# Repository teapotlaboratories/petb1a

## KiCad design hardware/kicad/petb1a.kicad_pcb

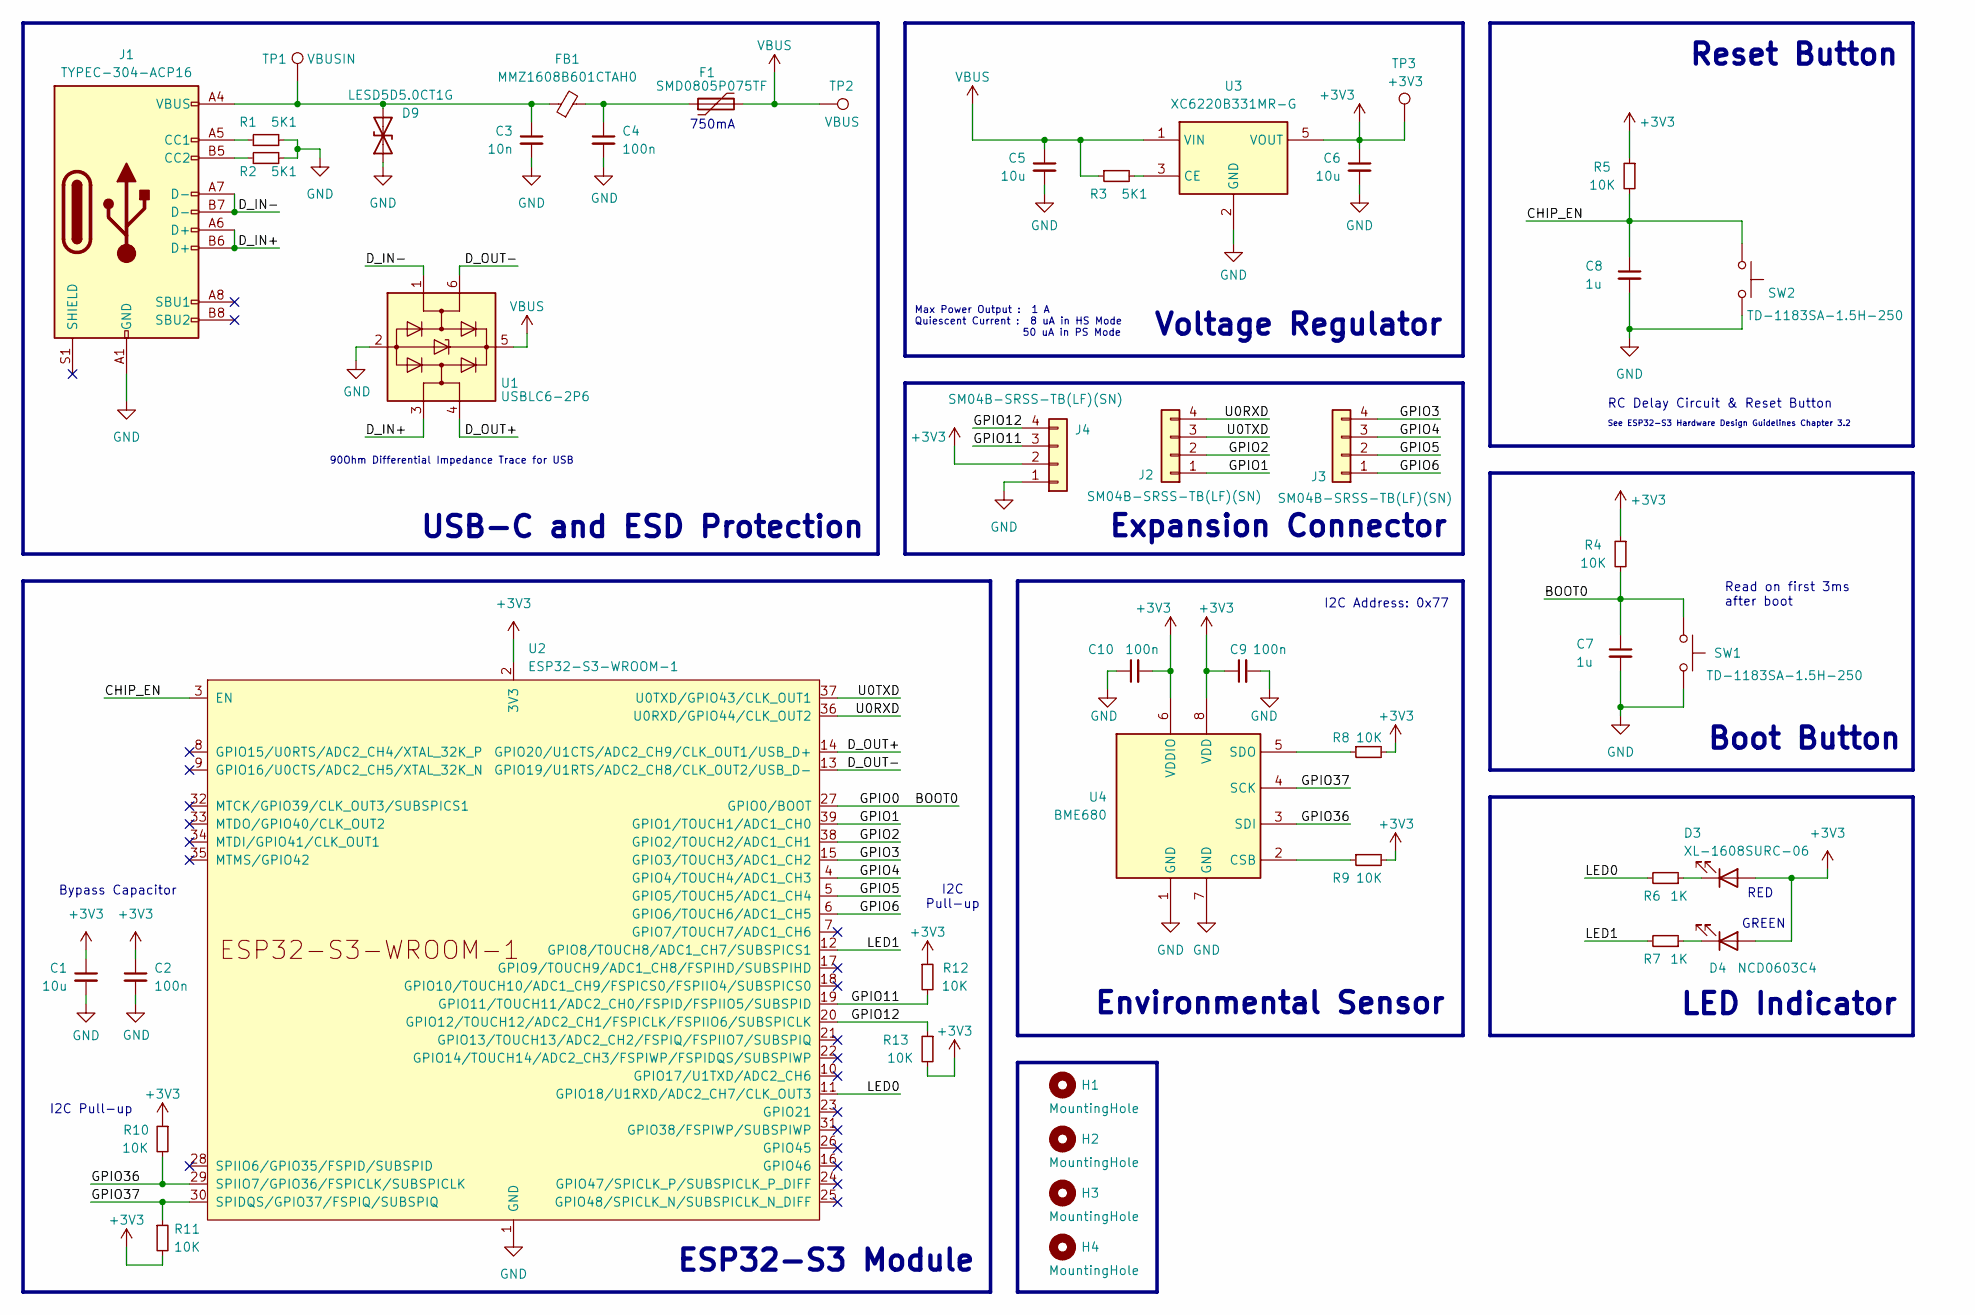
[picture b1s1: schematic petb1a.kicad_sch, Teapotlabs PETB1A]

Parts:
C1, C5, C6: 10u; C_0603_1608Metric; Manufacturer Part Number CL10A106KP8NNNC
C2, C4: 100n; C_0603_1608Metric; Manufacturer Part Number CL10B104KB8NNNC
C3: 10n; C_0603_1608Metric; Manufacturer Part Number CC0603KRX7R9BB103
C7, C8: 1u; C_0402_1005Metric; Manufacturer Part Number GRM155Z71A105KE01D
C9, C10: 100n; C_0402_1005Metric; Manufacturer Part Number GRM155R71H104KE14D
D3: XL-1608SURC-06; LED_0603_1608Metric; Manufacturer Part Number XL-1608SURC-06
D4: NCD0603C4; LED_0603_1608Metric; Manufacturer Part Number NCD0603C4
D9: LESD5D5.0CT1G; D_SOD-523; Manufacturer Part Number LESD5D5.0CT1G
F1: SMD0805P075TF; Fuse_0805_2012Metric; Manufacturer Part Number SMD0805P075TF
FB1: MMZ1608B601CTAH0; L_0603_1608Metric; Manufacturer Part Number MMZ1608B601CTAH0
H1, H2, H3, H4: MountingHole; MountingHole_3.2mm_M3
J1: TYPEC-304-ACP16; USB-C-SMD_TYPE-C-16P-1; Manufacturer Part Number TYPEC-304-ACP16
J2, J3, J4: SM04B-SRSS-TB(LF)(SN); JST_SH_SM04B-SRSS-TB_1x04-1MP_P1.00mm_Horizontal; Manufacturer Part Number SM04B-SRSS-TB(LF)(SN)
R1, R2, R3: 5K1; R_0402_1005Metric; Manufacturer Part Number 0402WGF5101TCE
R4, R5, R8, R9, R10, R11, R12, R13: 10K; R_0402_1005Metric; Manufacturer Part Number 0402WGF1002TCE
R6, R7: 1K; R_0603_1608Metric; Manufacturer Part Number RC0603FR-071KL
SW1, SW2: TD-1183SA-1.5H-250; KEY-SMD_L3.0-W2.5-LS4.0; Manufacturer Part Number TD-1183SA-1.5H-250
TP1: VBUSIN; TestPoint_Pad_D1.0mm
TP2: VBUS; TestPoint_Pad_D1.0mm
TP3: +3V3; TestPoint_Pad_D1.0mm
U1: USBLC6-2P6; SOT-666; Manufacturer Part Number USBLC6-2P6
U2: ESP32-S3-WROOM-1; Manufacturer Part Number ESP32-S3-WROOM-1-N16R8
U3: XC6220B331MR-G; SOT-23-5; Manufacturer Part Number XC6220B331MR-G
U4: BME680; Bosch_LGA-8_3x3mm_P0.8mm_ClockwisePinNumbering; Manufacturer Part Number BME688

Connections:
+3V3: C1.1, C2.1, C6.1, C9.1, C10.2, D3.2 (A), D4.2 (A), J4.2, R4.1, R5.1, R8.2, R9.2, R10.1, R11.2, R12.1, R13.2, TP3.1, U2.2 (3V3), U3.5 (VOUT), U4.6 (VDDIO), U4.8 (VDD)
/BOOT0: C7.1, R4.2, SW1.2, U2.27 (GPIO0/BOOT)
/CHIP_EN: C8.1, R5.2, SW2.2, U2.3 (EN)
/D_IN+: J1.A6 (D+), J1.B6 (D+), U1.3 (I/O2)
/D_IN-: J1.A7 (D-), J1.B7 (D-), U1.1 (I/O1)
/D_OUT+: U1.4 (I/O2), U2.14 (GPIO20/U1CTS/ADC2_CH9/CLK_OUT1/USB_D+)
/D_OUT-: U1.6 (I/O1), U2.13 (GPIO19/U1RTS/ADC2_CH8/CLK_OUT2/USB_D-)
/GPIO1: J2.1, U2.39 (GPIO1/TOUCH1/ADC1_CH0)
/GPIO2: J2.2, U2.38 (GPIO2/TOUCH2/ADC1_CH1)
/GPIO3: J3.4, U2.15 (GPIO3/TOUCH3/ADC1_CH2)
/GPIO4: J3.3, U2.4 (GPIO4/TOUCH4/ADC1_CH3)
/GPIO5: J3.2, U2.5 (GPIO5/TOUCH5/ADC1_CH4)
/GPIO6: J3.1, U2.6 (GPIO6/TOUCH6/ADC1_CH5)
/GPIO11: J4.3, R12.2, U2.19 (GPIO11/TOUCH11/ADC2_CH0/FSPID/FSPIIO5/S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)
/GPIO12: J4.4, R13.1, U2.20 (GPIO12/TOUCH12/ADC2_CH1/FSPICLK/FSPIIO6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)
/GPIO36: R10.2, U2.29 (SPIIO7/GPIO36/FSPICLK/SUBSPICLK), U4.3 (SDI)
/GPIO37: R11.1, U2.30 (SPIDQS/GPIO37/FSPIQ/SUBSPIQ), U4.4 (SCK)
/LED0: R6.2, U2.11 (GPIO18/U1RXD/ADC2_CH7/CLK_OUT3)
/LED1: R7.2, U2.12 (GPIO8/TOUCH8/ADC1_CH7/SUBSPICS1)
/U0RXD: J2.4, U2.36 (U0RXD/GPIO44/CLK_OUT2)
/U0TXD: J2.3, U2.37 (U0TXD/GPIO43/CLK_OUT1)
GND: C1.2, C2.2, C3.2, C4.2, C5.2, C6.2, C7.2, C8.2, C9.2, C10.1, J1.A1 (GND), J1.A12 (GND), J1.B1 (GND), J1.B12 (GND), J4.1, R1.2, R2.2, SW1.1, SW2.1, U1.2 (GND), U2.1 (GND), U2.40 (GND), U2.41 (GND), U3.2 (GND), U4.1 (GND), U4.7 (GND); also elsewhere on the board
unnamed: C4.1, F1.1, FB1.2
unnamed 23: C3.1, FB1.1, J1.A4 (VBUS), J1.A9 (VBUS), J1.B4 (VBUS), J1.B9 (VBUS), TP1.1; also elsewhere on the board
unnamed: D3.1 (K), R6.1
unnamed: D4.1 (K), R7.1
unnamed: J1.A5 (CC1), R1.1
unnamed: J1.B5 (CC2), R2.1
unnamed: R3.2, U3.3 (CE)
unnamed: R9.1, U4.2 (CSB)
unnamed: R8.1, U4.5 (SDO)
VBUS: C5.1, F1.2, R3.1, TP2.1, U1.5 (VBUS), U3.1 (VIN)

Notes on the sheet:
LED Indicator
Expansion Connector
Max Power Output : 1 A Quiescent Current : 8 uA in HS Mode 50 uA in PS Mode
RC Delay Circuit & Reset Button
I2C Pull-up
Environmental Sensor
RED
Boot Button
Reset Button
90Ohm Differential Impedance Trace for USB
Bypass Capacitor
I2C Address: 0x77
USB-C and ESD Protection
Voltage Regulator
I2C Pull-up
ESP32-S3 Module
Read on first 3ms after boot
See ESP32-S3 Hardware Design Guidelines Chapter 3.2
750mA
GREEN

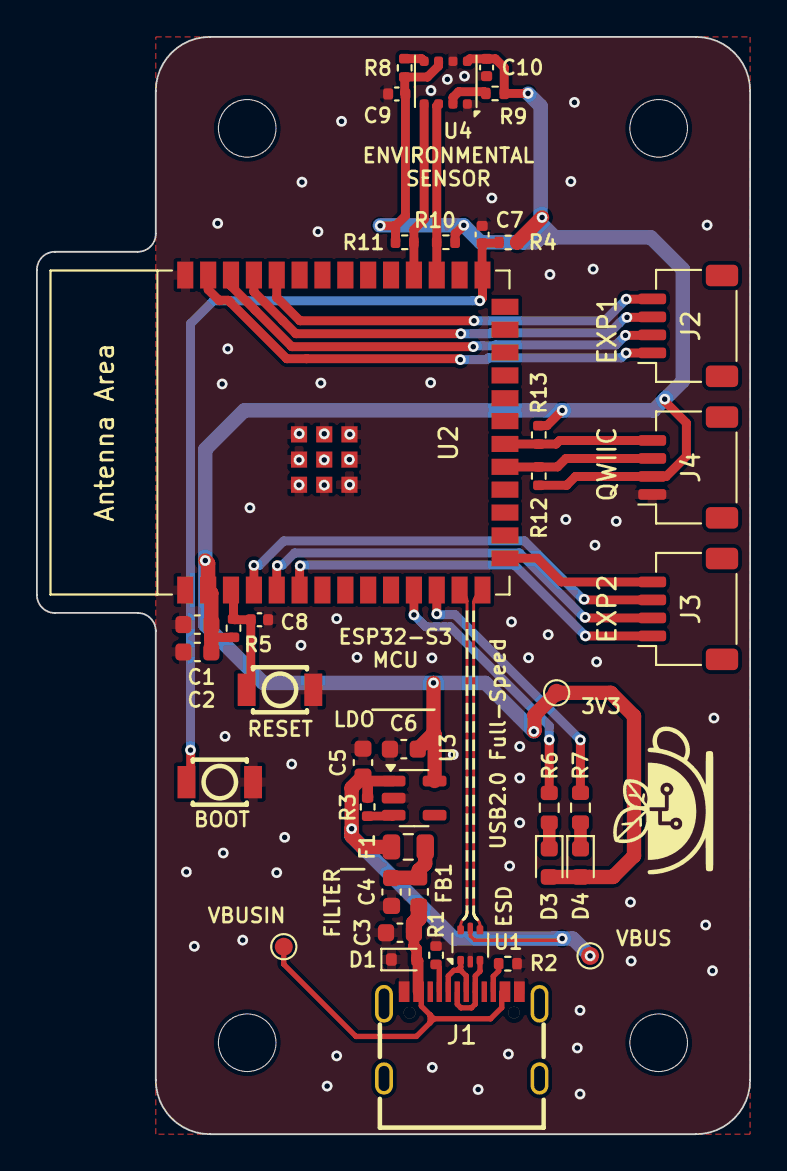
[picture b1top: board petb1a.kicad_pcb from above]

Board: 4 copper layers, 39.6 x 61.0 mm, 45 parts (0 on the bottom side), 32 nets.

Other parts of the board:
D1: LESD5D5.0CT1G; D_SOD-523

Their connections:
GND: D1.1 (A1); also elsewhere on the board
unnamed 23: D1.2 (A2); also elsewhere on the board

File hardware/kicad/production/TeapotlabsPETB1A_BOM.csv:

Id,Designator,Quantity,Manufacturer,Manufacturer Part Number,Value,Description,Footprint,Type,Distributor,Distributor Part Number,Distributor Link,Datasheet
1,"C1,C5,C6",3,Samsung Electro-Mechanics,CL10A106KP8NNNC,10u,Ceramic Capacitor 10V 10uF X5R ±10%,C_0603_1608Metric,SMD,LCSC,C19702,https://www.lcsc.com/product-detail/Multilayer-Ceramic-Capac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,https://datasheet.lcsc.com/lcsc/2304140030_Samsung-Electro-M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
2,"C2,C4",2,Samsung Electro-Mechanics,CL10B104KB8NNNC,100n,Ceramic Capacitor 50V 100nF X7R ±10%,C_0603_1608Metric,SMD,LCSC,C1591,https://www.lcsc.com/product-detail/Multilayer-Ceramic-Capac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,https://datasheet.lcsc.com/lcsc/2304140030_Samsung-Electro-M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
3,C3,1,YAGEO,CC0603KRX7R9BB103,10n,Ceramic Capacitors 50V 10nF X7R ±10%,C_0603_1608Metric,SMD,LCSC,C100042,https://www.lcsc.com/product-detail/Multilayer-Ceramic-Capac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,https://datasheet.lcsc.com/lcsc/2304140030_YAGEO-CC0603KRX7R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
4,"C7,C8",2,Murata Electronics,GRM155Z71A105KE01D,1u,Ceramic Capacitors 10V 1uF X7R ±10%,C_0402_1005Metric,SMD,LCSC,C528974,https://www.lcsc.com/product-detail/Multilayer-Ceramic-Capac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,https://datasheet.lcsc.com/lcsc/2005261833_Murata-Electronic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
5,"C9,C10",2,Murata Electronics,GRM155R71H104KE14D,100n,Ceramic Capacitors 50V 100nF X7R,C_0402_1005Metric,SMD,LCSC,C77020,https://www.lcsc.com/product-detail/Multilayer-Ceramic-Capac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,https://datasheet.lcsc.com/lcsc/1809272047_Murata-Electronic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
6,D1,1,LRC,LESD5D5.0CT1G,LESD5D5.0CT1G,ESD 9.4A 18.6V 5.6V Bi-Directional 5V,D_SOD-523,SMD,LCSC,C383211,https://www.lcsc.com/product-detail/Electrostatic-and-Surge-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,https://datasheet.lcsc.com/lcsc/1912111437_LRC-LESD5D5-0CT1G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
7,D3,1,XINGLIGHT,XL-1608SURC-06,XL-1608SURC-06,LED Red 120° 55mW 25mA ,LED_0603_1608Metric,SMD,LCSC,C965799,https://www.lcsc.com/product-detail/Light-Emitting-Diodes-sp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,https://datasheet.lcsc.com/lcsc/2402181505_XINGLIGHT-XL-1608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
8,D4,1,Foshan NationStar Optoelectronics,NCD0603C4,NCD0603C4,LED Green-yellow 140° 65mW 1.6V~2.6V,LED_0603_1608Metric,SMD,LCSC,C7429911,https://www.lcsc.com/product-detail/Light-Emitting-Diodes-sp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,https://datasheet.lcsc.com/lcsc/2306200951_Foshan-NationStar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
9,F1,1,RUILON(Shenzhen Ruilongyuan Elec),SMD0805P075TF,SMD0805P075TF,Resettable Fuses 6V 750mA 40A 1.5A,Fuse_0805_2012Metric,SMD,LCSC,C20979,https://www.lcsc.com/product-detail/Resettable-Fuses_RUILON-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,https://datasheet.lcsc.com/lcsc/2304140030_RUILON-Shenzhen-R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
10,FB1,1,TDK,MMZ1608B601CTAH0,MMZ1608B601CTAH0,Ferrite Beads 400mΩ ±25% 600Ω@100MHz,L_0603_1608Metric,SMD,LCSC,C97120,https://www.lcsc.com/product-detail/Ferrite-Beads_TDK-MMZ160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,https://datasheet.lcsc.com/lcsc/2304140030_TDK-MMZ1608B601CT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
11,J1,1,XUNPU,TYPEC-304-ACP16,TYPEC-304-ACP16,Type-C SMD 3A 1 Surface Mount，Right Angle 16P Female,USB-C-SMD_TYPE-C-16P-1,SMD,LCSC,C2982555,https://www.lcsc.com/product-detail/USB-Connectors_XUNPU-TYP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,https://datasheet.lcsc.com/lcsc/2203111830_XUNPU-TYPEC-304-A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
12,"J2,J3,J4",3,JST,SM04B-SRSS-TB(LF)(SN), SM04B-SRSS-TB(LF)(SN),Right Angle Wire To Board 1x4P 4P 1mm 1A,JST_SH_SM04B-SRSS-TB_1x04-1MP_P1.00mm_Horizontal,SMD,LCSC,C160404,https://www.lcsc.com/product-detail/Wire-To-Board-Wire-To-Wi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,https://datasheet.lcsc.com/lcsc/2304140030_JST-Sales-America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
13,"R1,R2,R3",3,UNI-ROYAL(Uniroyal Elec),0402WGF5101TCE,5K1,Resistor 62.5mW ±1% 5.1kΩ,R_0402_1005Metric,SMD,LCSC,C25905,https://www.lcsc.com/product-detail/Chip-Resistor-Surface-Mo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,https://datasheet.lcsc.com/lcsc/2206010045_UNI-ROYAL-Uniroya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
14,"R4,R5,R8,R9,R10,R11,R12,R13",8,UNI-ROYAL(Uniroyal Elec),0402WGF1002TCE,10K,Resistors 62.5mW ±1% 10kΩ,R_0402_1005Metric,SMD,LCSC,C25744,https://www.lcsc.com/product-detail/Chip-Resistor-Surface-Mo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,https://datasheet.lcsc.com/lcsc/2206010100_UNI-ROYAL-Uniroya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
15,"R6,R7",2,YAGEO,RC0603FR-071KL,1K,Resistor 100mW 75V ±1% 1kΩ,R_0603_1608Metric,SMD,LCSC,C22548,https://www.lcsc.com/product-detail/Chip-Resistor-Surface-Mo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,https://datasheet.lcsc.com/lcsc/2304140030_YAGEO-RC0603FR-07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
16,"SW1,SW2",2,DEALON,TD-1183SA-1.5H-250,TD-1183SA-1.5H-250,"Tactile Switches 2.5mm 1.5mm 3mm SMD,2.5x3mm ",KEY-SMD_L3.0-W2.5-LS4.0,SMD,LCSC,C2905189,https://www.lcsc.com/product-detail/Tactile-Switches_DEALON-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,https://datasheet.lcsc.com/lcsc/2209081200_DEALON-TD-1183SA-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
17,U1,1,STMicroelectronics,USBLC6-2P6,USBLC6-2P6,ESD Protection 6V 17V 2 Unidirectional 5.25V,SOT-666,SMD,LCSC,C15999,https://www.lcsc.com/product-detail/ESD-Protection-Devices_S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,https://www.st.com/resource/en/datasheet/usblc6-2.pdf
18,U2,1,Espressif Systems,ESP32-S3-WROOM-1-N16R8 ,ESP32-S3-WROOM-1,WiFi Modules ESP32-S3 ,ESP32-S3-WROOM-1,SMD,LCSC,C2913202,https://www.lcsc.com/product-detail/WiFi-Modules_Espressif-S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,https://www.espressif.com/sites/default/files/documentation/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
19,U3,1,Torex Semicon,XC6220B331MR-G,XC6220B331MR-G,LDO 50dB@(1kHz) 1A Fixed 3.3V Positive,SOT-23-5,SMD,LCSC,C86534,https://www.lcsc.com/product-detail/Linear-Voltage-Regulator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,https://datasheet.lcsc.com/lcsc/1810010324_Torex-Semicon-XC6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
20,U4,1,Bosch Sensortec,BME688,BME680,"4-in-1 sensor, gas, humidity, pressure, temperature, I2C and SPI interface, 1.71-3.6V, LGA-8",Bosch_LGA-8_3x3mm_P0.8mm_ClockwisePinNumbering,SMD,LCSC,C3664478,https://www.lcsc.com/product-detail/Temperature-and-Humidity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,https://ae-bst.resource.bosch.com/media/_tech/media/datashee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

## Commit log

2024-02-19 initial kicad file
2024-02-19 add usb-c and filter
2024-02-20 add reset, boot, ldo and bypass cap
2024-02-21 update schematic
2024-02-22 update schematics
2024-02-22 change socket to header
2024-02-23 intial pcb wiring
2024-02-23 update pcb layout
2024-02-24 update pcb
2024-02-27 update board
2024-02-28 revision 1 design
2024-02-28 update manufacturing info
